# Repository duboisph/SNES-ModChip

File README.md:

SNES-ModChip
============

Eagle schematics for custom PCB with SNES SuperCIC & IGR (https://github.com/mrehkopf/sd2snes).

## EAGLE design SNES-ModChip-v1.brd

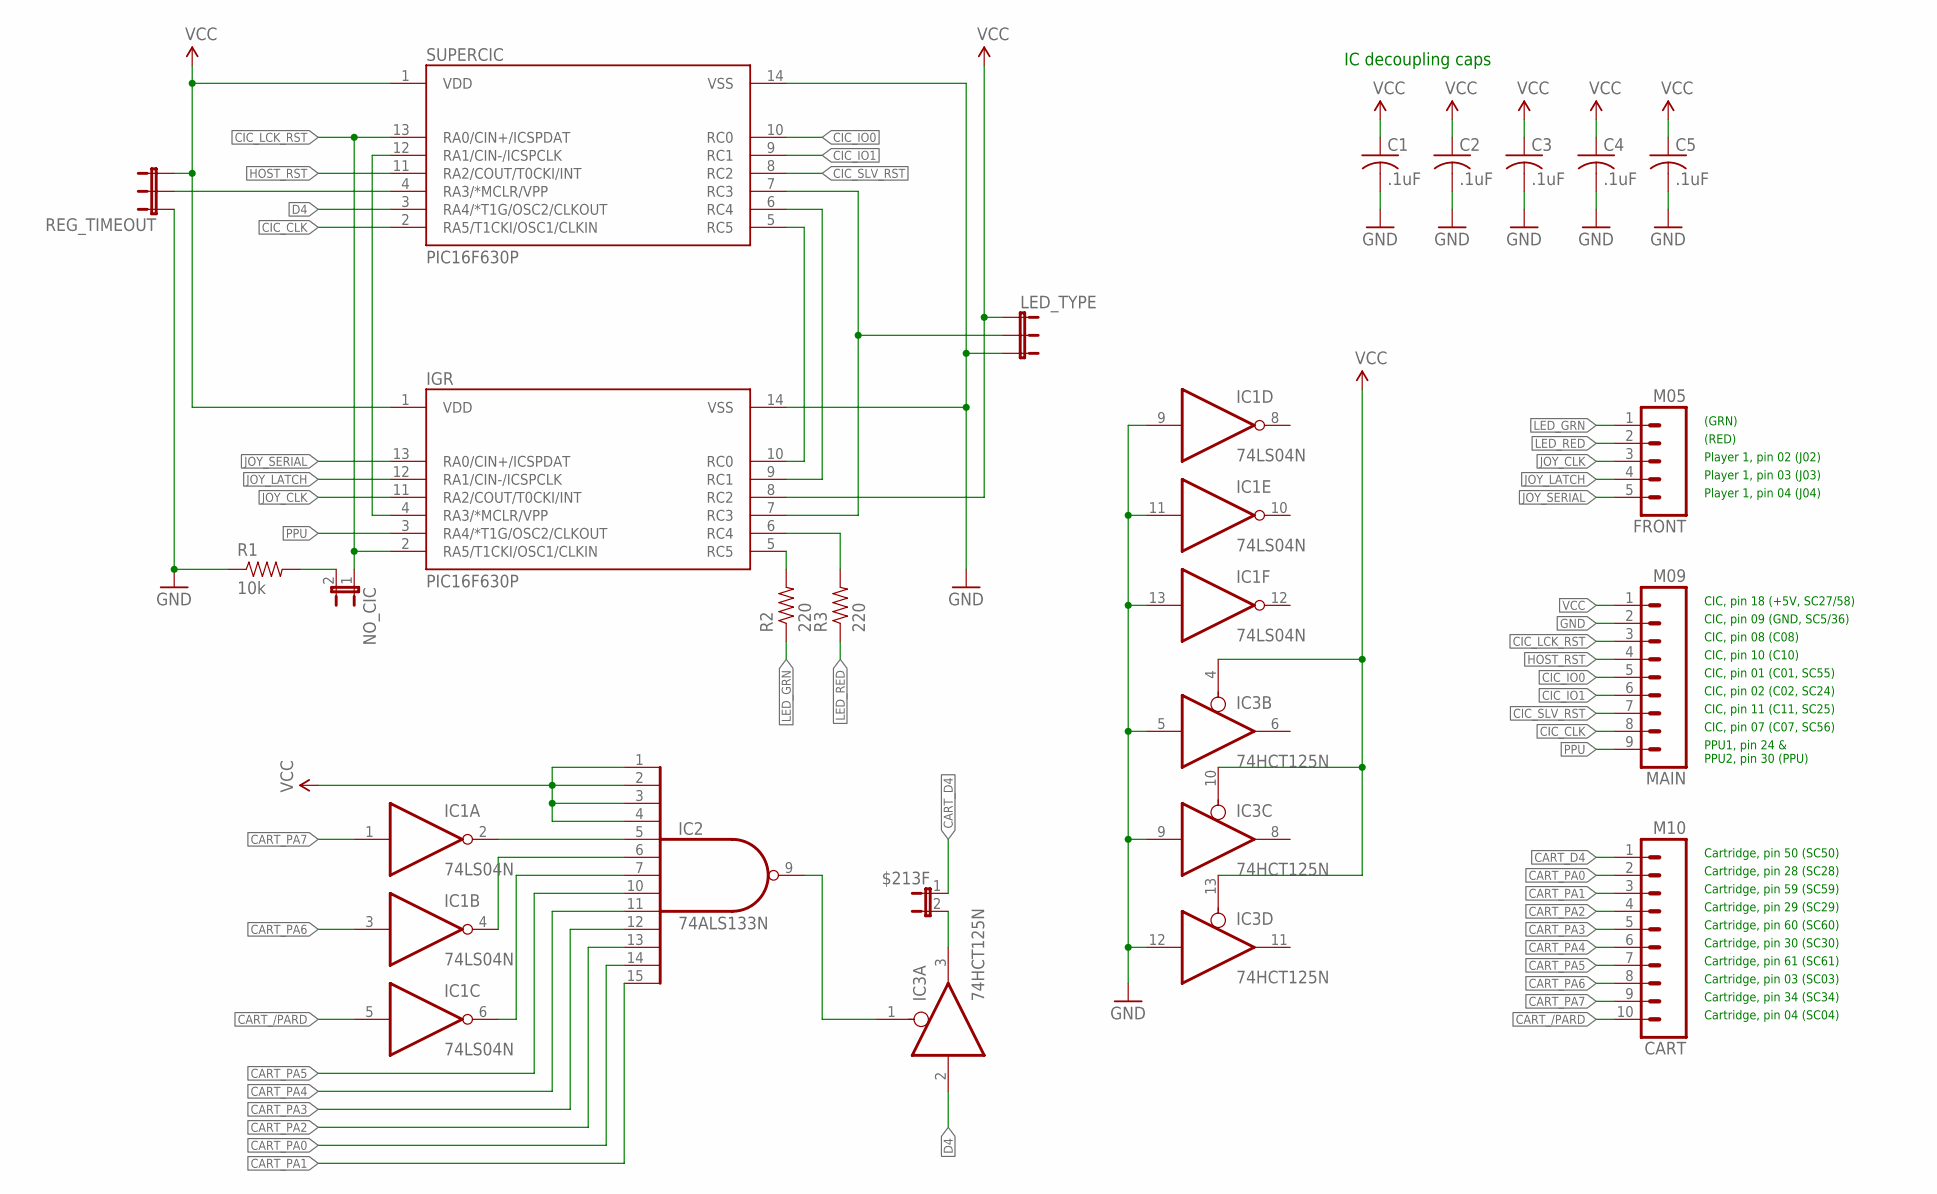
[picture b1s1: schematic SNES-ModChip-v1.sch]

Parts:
$213F: JUMPER-2PTH; 1X02
C1, C2, C3, C4, C5: .1uF; C050-025X075
CART: M10; 1X10
FRONT: M05; 1X05
IC1: 74LS04N; DIL14
IC2: 74ALS133N; DIL16
IC3: 74HCT125N; DIL14
IGR: PIC16F630P; DIL14
LED_TYPE: JUMPER-3PTH; 1X03
MAIN: M09; 1X09
NO_CIC: JUMPER-2PTH; 1X02
R1: 10k; AXIAL-0.3
R2, R3: 220; AXIAL-0.3
REG_TIMEOUT: JUMPER-3PTH; 1X03
SUPERCIC: PIC16F630P; DIL14

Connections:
CART_/PARD: CART.10, IC1.5 (I)
CART_D4: $213F.1, CART.1
CART_PA0: CART.2, IC2.14 (I11)
CART_PA1: CART.3, IC2.15 (I12)
CART_PA2: CART.4, IC2.13 (I10)
CART_PA3: CART.5, IC2.12 (I9)
CART_PA4: CART.6, IC2.11 (I8)
CART_PA5: CART.7, IC2.10 (I7)
CART_PA6: CART.8, IC1.3 (I)
CART_PA7: CART.9, IC1.1 (I)
CIC_CLK: MAIN.8, SUPERCIC.2 (RA5/T1CKI/OSC1/CLKIN)
CIC_IO0: MAIN.5, SUPERCIC.10 (RC0)
CIC_IO1: MAIN.6, SUPERCIC.9 (RC1)
CIC_LCK_RST: IGR.2 (RA5/T1CKI/OSC1/CLKIN), MAIN.3, NO_CIC.1, SUPERCIC.13 (RA0/CIN+/ICSPDAT)
CIC_SLV_RST: MAIN.7, SUPERCIC.8 (RC2)
D4: IC3.2 (I), SUPERCIC.3 (RA4/*T1G/OSC2/CLKOUT)
GND: C1.2, C2.2, C3.2, C4.2, C5.2, IC1.7 (GND), IC1.9 (I), IC1.11 (I), IC1.13 (I), IC2.8 (GND), IC3.5 (I), IC3.7 (GND), IC3.9 (I), IC3.12 (I), IGR.14 (VSS), LED_TYPE.3, MAIN.2, R1.P$1 (1), REG_TIMEOUT.1, SUPERCIC.14 (VSS)
HOST_RST: MAIN.4, SUPERCIC.11 (RA2/COUT/T0CKI/INT)
JOY_CLK: FRONT.3, IGR.11 (RA2/COUT/T0CKI/INT)
JOY_LATCH: FRONT.4, IGR.12 (RA1/CIN-/ICSPCLK)
JOY_SERIAL: FRONT.5, IGR.13 (RA0/CIN+/ICSPDAT)
LED_GRN: FRONT.1, R2.P$1 (1)
LED_RED: FRONT.2, R3.P$1 (1)
unnamed: IGR.10 (RC0), SUPERCIC.5 (RC5)
unnamed: IGR.9 (RC1), SUPERCIC.6 (RC4)
unnamed: IC1.2 (O), IC2.5 (I4)
unnamed: IGR.4 (RA3/*MCLR/VPP), SUPERCIC.12 (RA1/CIN-/ICSPCLK)
unnamed: IC1.4 (O), IC2.6 (I5)
unnamed: IC1.6 (O), IC2.7 (I6)
unnamed: REG_TIMEOUT.2, SUPERCIC.4 (RA3/*MCLR/VPP)
unnamed: IGR.7 (RC3), LED_TYPE.2, SUPERCIC.7 (RC3)
unnamed: NO_CIC.2, R1.P$2 (2)
unnamed: $213F.2, IC3.3 (O)
unnamed: IGR.5 (RC5), R2.P$2 (2)
unnamed: IGR.6 (RC4), R3.P$2 (2)
unnamed: IC2.9 (O), IC3.1 (OE)
PPU: IGR.3 (RA4/*T1G/OSC2/CLKOUT), MAIN.9
VCC: C1.1, C2.1, C3.1, C4.1, C5.1, IC1.14 (VCC), IC2.1 (I0), IC2.2 (I1), IC2.3 (I2), IC2.4 (I3), IC2.16 (VCC), IC3.4 (OE), IC3.10 (OE), IC3.13 (OE), IC3.14 (VCC), IGR.1 (VDD), IGR.8 (RC2), LED_TYPE.1, MAIN.1, REG_TIMEOUT.3, SUPERCIC.1 (VDD)

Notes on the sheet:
Player 1, pin 02 (J02)
Player 1, pin 03 (J03)
Player 1, pin 04 (J04)
CIC, pin 01 (C01, SC55)
CIC, pin 02 (C02, SC24)
CIC, pin 07 (C07, SC56)
CIC, pin 08 (C08)
CIC, pin 10 (C10)
CIC, pin 11 (C11, SC25)
Cartridge, pin 28 (SC28)
Cartridge, pin 59 (SC59)
Cartridge, pin 29 (SC29)
Cartridge, pin 60 (SC60)
Cartridge, pin 30 (SC30)
Cartridge, pin 61 (SC61)
Cartridge, pin 03 (SC03)
Cartridge, pin 34 (SC34)
Cartridge, pin 04 (SC04)
CIC, pin 18 (+5V, SC27/58)
CIC, pin 09 (GND, SC5/36)
Cartridge, pin 50 (SC50)
PPU1, pin 24 & PPU2, pin 30 (PPU)
(GRN)
(RED)
IC decoupling caps

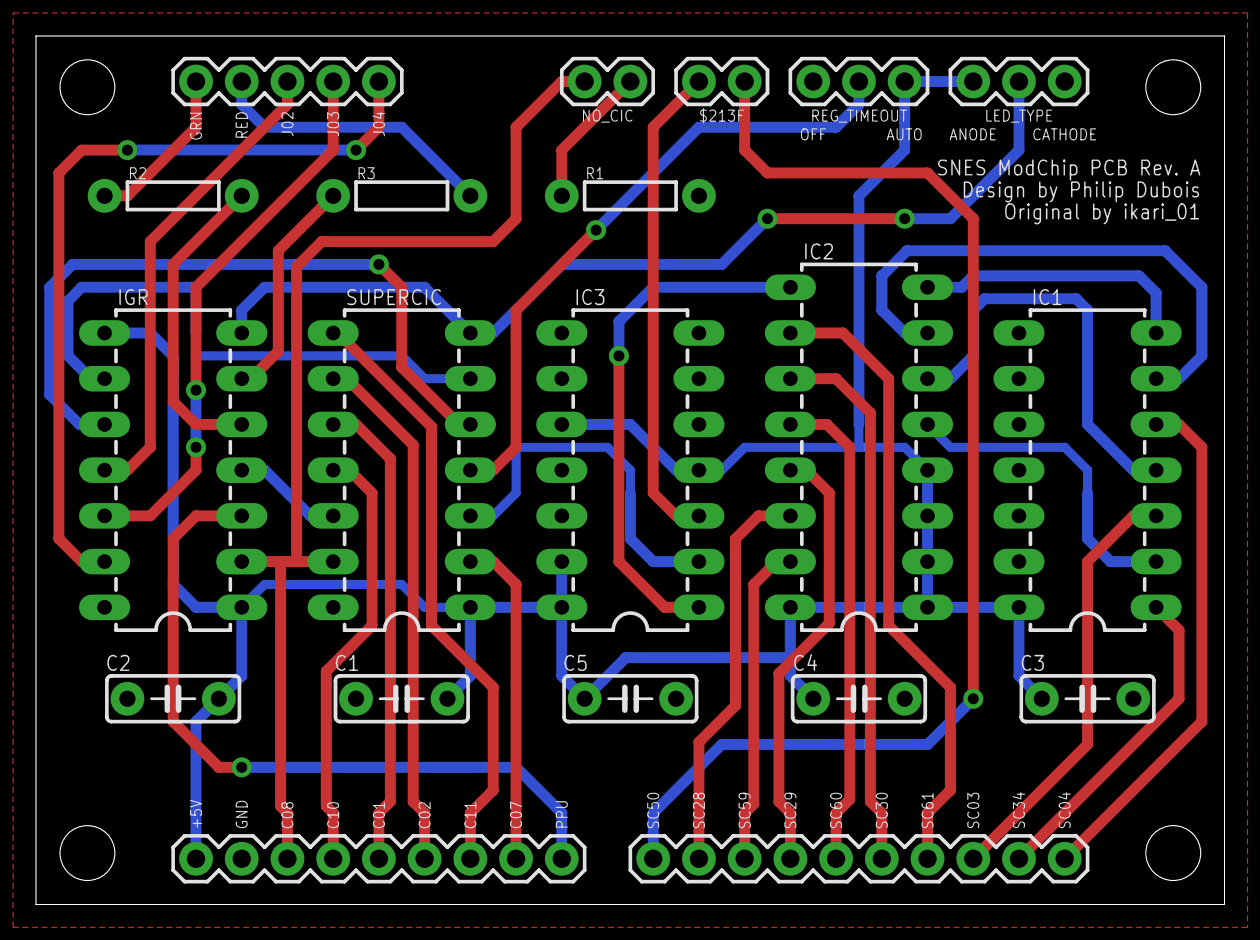
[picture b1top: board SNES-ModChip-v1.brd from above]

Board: 2 copper layers, 66.0 x 48.2 mm, 20 parts (0 on the bottom side), 38 nets.

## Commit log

2014-06-01 First board revision
2014-06-01 Added minimal README

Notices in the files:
parts and their libraries:
SparkFun-Passives: Licensing: Creative Commons ShareAlike 4.0 International - https://creativecommons.org/licenses/by-sa/4.0
